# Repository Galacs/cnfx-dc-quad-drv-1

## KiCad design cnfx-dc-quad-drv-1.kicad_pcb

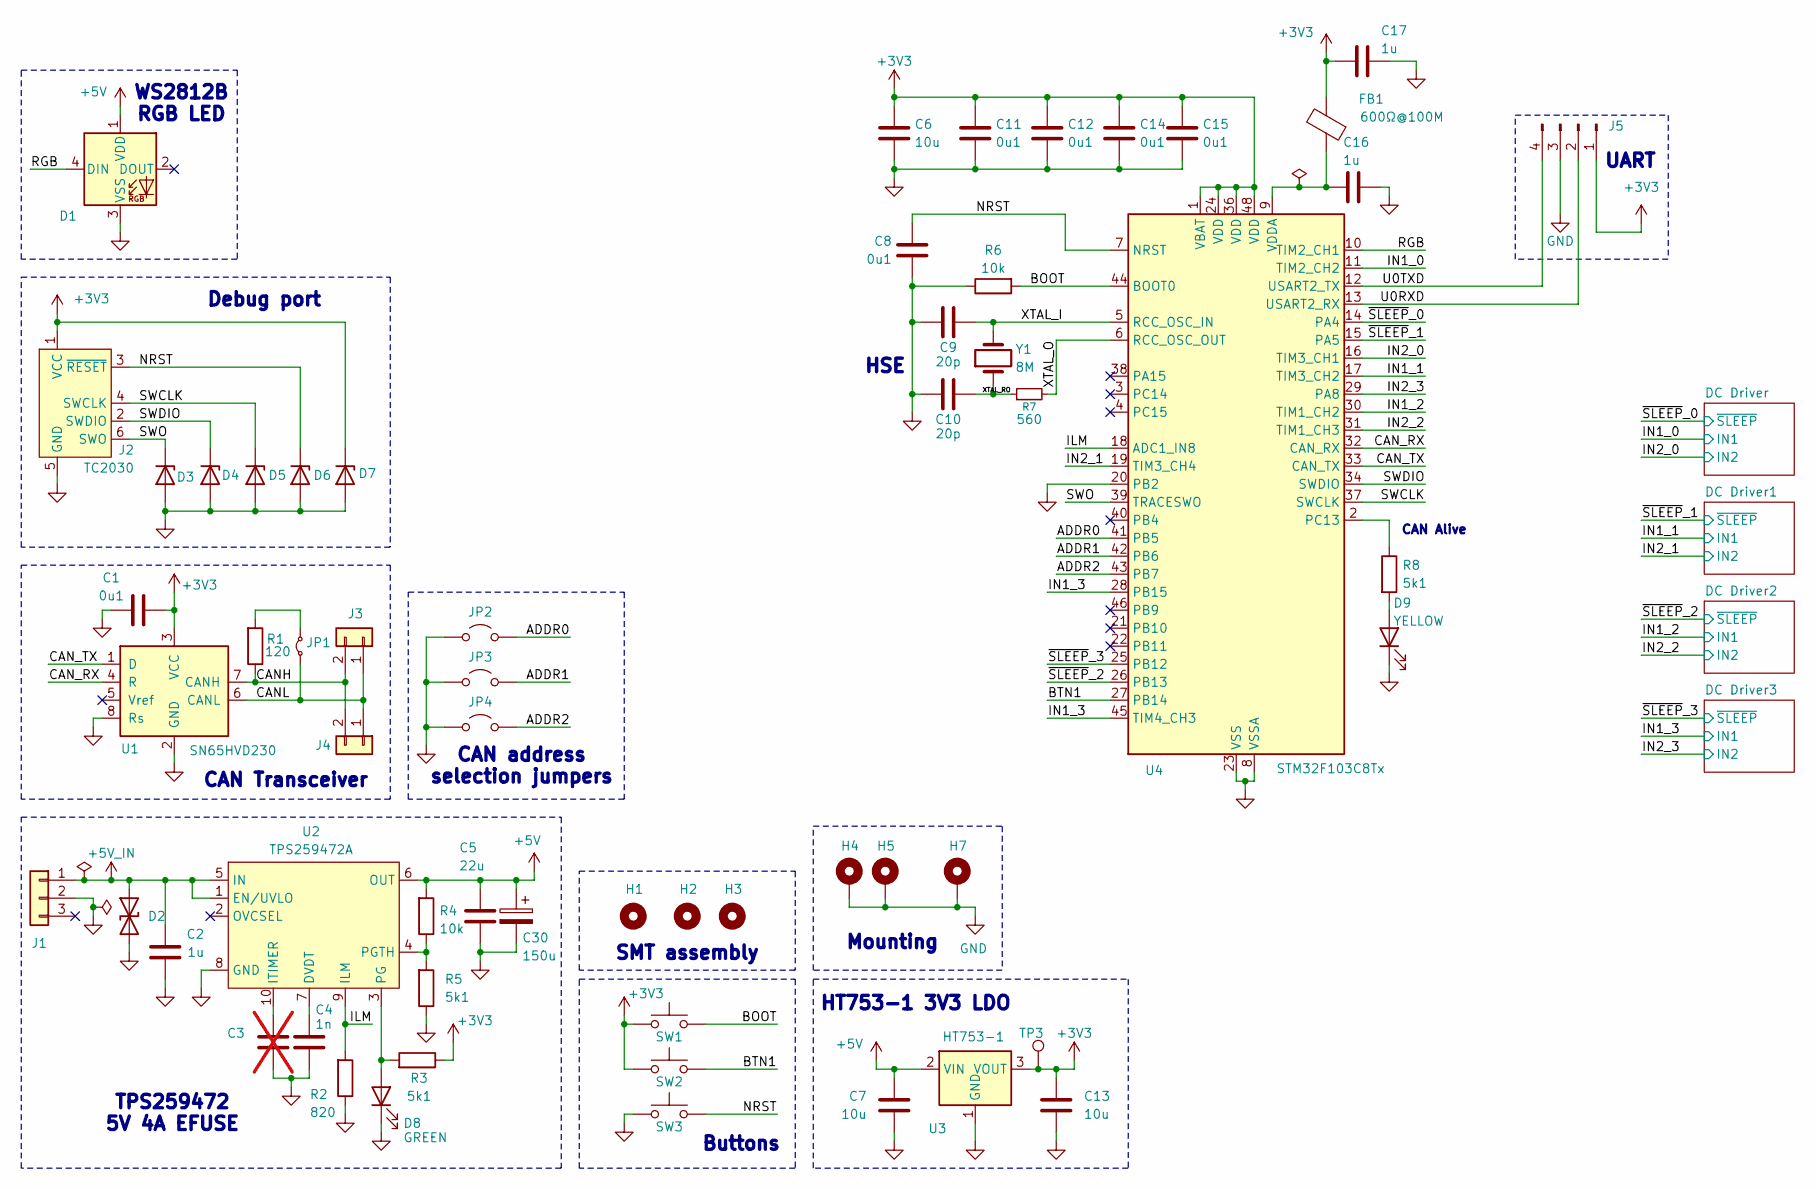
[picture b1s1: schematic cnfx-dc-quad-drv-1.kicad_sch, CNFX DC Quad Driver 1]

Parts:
C1, C8, C11, C12, C14, C15: 0u1; C_0402_1005Metric; Manufacturer Part Number CL05B104KB54PNC; JLCPCB Part # C307331
C2, C16, C17: 1u; C_0402_1005Metric; Manufacturer Part Number CL05A105KA5NQNC; JLCPCB Part # C52923
C3: C; C_0402_1005Metric; not fitted
C4: 1n; C_0402_1005Metric; Manufacturer Part Number 0402B102K500NT; JLCPCB Part # C1523
C5: 22u; C_0805_2012Metric; Manufacturer Part Number CL21A226MAQNNNE; JLCPCB Part # C45783
C6, C7, C13: 10u; C_0805_2012Metric; Manufacturer Part Number GRM21BR61H106KE43L; JLCPCB Part # C440198
C9, C10: 20p; C_0603_1608Metric; Manufacturer Part Number CL10C200JB8NNNC; JLCPCB Part # C1648
C30: 150u; CP_Elec_6.3x7.7; Manufacturer Part Number EEEFTV151XAP; JLCPCB Part # C178603
D1: WS2812B; LED_WS2812B_PLCC4_5.0x5.0mm_P3.2mm; Manufacturer Part Number WS2812B-V5/W; JLCPCB Part # C2874885
D2: SMAJ6.0CA; D_SMA; Manufacturer Part Number SMAJ6.0CA; JLCPCB Part # C19077526
D3, D4, D5, D6, D7: H5VU10U; Diode_DFN1006; Manufacturer Part Number H5VU10U; JLCPCB Part # C22395519
D8: GREEN; LED_0805_2012Metric; Manufacturer Part Number KT-0805G; JLCPCB Part # C2297
D9: YELLOW; LED_0805_2012Metric; Manufacturer Part Number KT-0805Y; JLCPCB Part # C2296
FB1: 600Ω@100M; L_0805_2012Metric; Manufacturer Part Number MPZ2012S601ATD25; JLCPCB Part # C81034
H1, H2, H3: MountingHole; ToolingHole_1.152mm
H4, H5, H7: MountingHole_Pad; MountingHole_3.2mm_M3_Pad_Via
J1: Conn_01x03; JST_XH_B3B-XH-A_1x03_P2.50mm_Vertical; Manufacturer Part Number B3B-XH-A(LF)(SN); JLCPCB Part # C144394
J2: TC2030; Tag-Connect_TC2030-IDC-NL_2x03_P1.27mm_Vertical
J3, J4: Conn_01x02; JST_XH_B2B-XH-A_1x02_P2.50mm_Vertical; Manufacturer Part Number B2B-XH-A(LF)(SN); JLCPCB Part # C158012
J5: Conn_01x04_Pin; PinHeader_1x04_P2.54mm_Vertical
JP1: Jumper_2_Small_Bridged; PinHeader_1x02_P2.54mm_Vertical
JP2, JP3, JP4: Jumper_2_Open; SolderJumper-2_P1.3mm_Open_RoundedPad1.0x1.5mm
R1: 120; R_1206_3216Metric; Manufacturer Part Number 1206W4F1200T5E; JLCPCB Part # C17909
R2: 820; R_0402_1005Metric; Manufacturer Part Number 0402WGF8200TCE; JLCPCB Part # C25135
R3, R5, R8: 5k1; R_0402_1005Metric; Manufacturer Part Number 0402WGF5101TCE; JLCPCB Part # C25905
R4, R6: 10k; R_0402_1005Metric; Manufacturer Part Number 0402WGF1002TCE; JLCPCB Part # C25744
R7: 560; R_0603_1608Metric; Manufacturer Part Number 0603WAF5600T5E; JLCPCB Part # C23204
SW1, SW2, SW3: SW_Push; SW_SPST_TS-1088-xR020; Manufacturer Part Number TS-1088-AR02016; JLCPCB Part # C720477
TP3: TestPoint; TestPoint_Pad_D2.0mm
U1: SN65HVD230; SOIC-8_3.9x4.9mm_P1.27mm; Manufacturer Part Number SN65HVD230DR; JLCPCB Part # C12084
U2: TPS259472A; Texas_RPW0010A_VQFN-HR-10_2x2mm_P0.5mm; Manufacturer Part Number TPS259472ARPWR; JLCPCB Part # C3662789
U3: HT753-1; SOT-89-3; Manufacturer Part Number HT7533-1; JLCPCB Part # C14289
U4: STM32F103C8Tx; LQFP-48_7x7mm_P0.5mm; Manufacturer Part Number STM32F103C8T6; JLCPCB Part # C8734
Y1: 8M; Crystal_SMD_5032-2Pin_5.0x3.2mm; Manufacturer Part Number X50328MSB2GI; JLCPCB Part # C115962

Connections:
+3V3: C1.1, C6.1, C11.1, C12.1, C13.1, C14.1, C15.1, C17.1, D7.1 (K), FB1.2, J2.1 (VCC), J5.1, R3.1, SW1.1, SW2.1, TP3.1 (1_1), U1.3 (VCC), U3.3 (VOUT), U4.1 (VBAT), U4.24 (VDD), U4.36 (VDD), U4.48 (VDD); also elsewhere on the board
+5V: C5.1, C7.1, C30.1, D1.1 (VDD), R4.2, U2.6 (OUT), U3.2 (VIN); also elsewhere on the board
+5V_IN: C2.2, D2.1 (A1), J1.1, U2.1 (EN/UVLO), U2.5 (IN)
/ADDR0: JP2.2 (B), U4.41 (PB5)
/ADDR1: JP3.2 (B), U4.42 (PB6)
/ADDR2: JP4.2 (B), U4.43 (PB7)
/BOOT: R6.2, SW1.2, U4.44 (BOOT0)
/BTN1: SW2.2, U4.27 (PB14)
/CANH: J3.2, J4.2, R1.1, U1.7 (CANH)
/CANL: J3.1, J4.1, JP1.1 (A), U1.6 (CANL)
/CAN_RX: U1.4 (R), U4.32 (CAN_RX)
/CAN_TX: U1.1 (D), U4.33 (CAN_TX)
/ILM: R2.2, U2.9 (ILM), U4.18 (ADC1_IN8)
/IN1_0: U4.11 (TIM2_CH2); also elsewhere on the board
/IN1_1: U4.17 (TIM3_CH2); also elsewhere on the board
/IN1_2: U4.30 (TIM1_CH2); also elsewhere on the board
/IN1_3: U4.28 (PB15), U4.45 (TIM4_CH3); also elsewhere on the board
/IN2_0: U4.16 (TIM3_CH1); also elsewhere on the board
/IN2_1: U4.19 (TIM3_CH4); also elsewhere on the board
/IN2_2: U4.31 (TIM1_CH3); also elsewhere on the board
/IN2_3: U4.29 (PA8); also elsewhere on the board
/NRST: C8.1, D6.1 (K), J2.3 (~RESET), SW3.2, U4.7 (NRST)
/RGB: D1.4 (DIN), U4.10 (TIM2_CH1)
/SWCLK: D5.1 (K), J2.4 (SWCLK), U4.37 (SWCLK)
/SWDIO: D4.1 (K), J2.2 (SWDIO), U4.34 (SWDIO)
/SWO: D3.1 (K), J2.6 (SWO), U4.39 (TRACESWO)
/U0RXD: J5.2, U4.13 (USART2_RX)
/U0TXD: J5.4, U4.12 (USART2_TX)
/XTAL_I: C9.1, U4.5 (RCC_OSC_IN), Y1.2
/XTAL_O: R7.2, U4.6 (RCC_OSC_OUT)
/XTAL_RO: C10.1, R7.1, Y1.1
/~SLEEP_0: U4.14 (PA4); also elsewhere on the board
/~SLEEP_1: U4.15 (PA5); also elsewhere on the board
/~SLEEP_2: U4.26 (PB13); also elsewhere on the board
/~SLEEP_3: U4.25 (PB12); also elsewhere on the board
GND: C1.2, C2.1, C3.2, C4.2, C5.2, C6.2, C7.2, C8.2, C9.2, C10.2, C11.2, C12.2, C13.2, C14.2, C15.2, C16.2, C17.2, C30.2, D1.3 (VSS), D2.2 (A2), D3.2 (A), D4.2 (A), D5.2 (A), D6.2 (A), D7.2 (A), D8.1 (K), D9.1 (K), H4.1 (1_1), H5.1 (1_1), H7.1 (1_1), J1.2, J2.5 (GND), J5.3, JP2.1 (A), JP3.1 (A), JP4.1 (A), R2.1, R5.1, R6.1, SW3.1, U1.2 (GND), U1.8 (Rs), U2.8 (GND), U3.1 (GND), U4.8 (VSSA), U4.20 (PB2), U4.23 (VSS), U4.35 (VSS), U4.47 (VSS); also elsewhere on the board
unnamed: D8.2 (A), R3.2, U2.3 (PG)
unnamed: D9.2 (A), R8.2
unnamed: JP1.2 (B), R1.2
unnamed: C4.1, U2.7 (DVDT)
unnamed: C3.1, U2.10 (ITIMER)
unnamed: R4.1, R5.2, U2.4 (PGTH)
unnamed: R8.1, U4.2 (PC13)
unnamed: C16.1, FB1.1, U4.9 (VDDA)

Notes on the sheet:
SMT assembly
CAN address selection jumpers
Debug port
TPS259472 5V 4A EFUSE
HT753-1 3V3 LDO
CAN Alive
UART
CAN Transceiver
Mounting
WS2812B RGB LED
Buttons
HSE

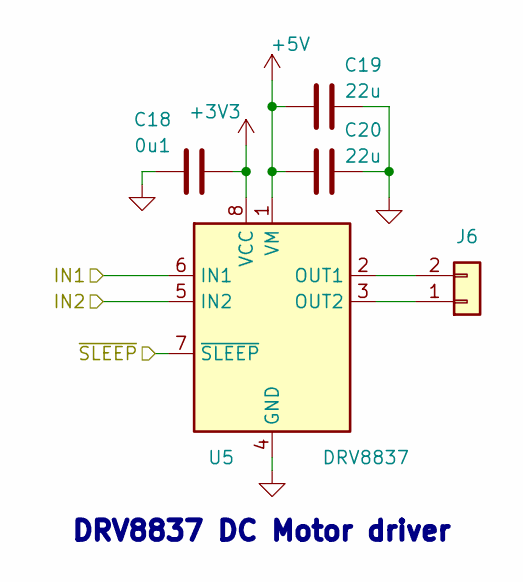
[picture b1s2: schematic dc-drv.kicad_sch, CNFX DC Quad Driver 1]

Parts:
C18: 0u1; C_0402_1005Metric; Manufacturer Part Number CL05B104KB54PNC; JLCPCB Part # C307331
C19, C20: 22u; C_0805_2012Metric; Manufacturer Part Number CL21A226MAQNNNE; JLCPCB Part # C45783
J6: Conn_01x02; JST_XH_B2B-XH-A_1x02_P2.50mm_Vertical; Manufacturer Part Number B2B-XH-A(LF)(SN); JLCPCB Part # C158012
U5: DRV8837; Texas_DSG0008A_WSON-8-1EP_2x2mm_P0.5mm_EP0.9x1.6mm_ThermalV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; Manufacturer Part Number DRV8837DSGR; JLCPCB Part # C39159

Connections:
+3V3: C18.2, U5.8 (VCC); also elsewhere on the board
+5V: C19.2, C20.2, U5.1 (VM); also elsewhere on the board
/IN1_0: U5.6 (IN1); also elsewhere on the board
/IN2_0: U5.5 (IN2); also elsewhere on the board
/~SLEEP_0: U5.7 (~SLEEP); also elsewhere on the board
GND: C18.1, C19.1, C20.1, U5.4 (GND), U5.9 (GND); also elsewhere on the board
unnamed: J6.1, U5.3 (OUT2)
unnamed: J6.2, U5.2 (OUT1)

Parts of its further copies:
C21, C24, C27: 0u1; C_0402_1005Metric; Manufacturer Part Number CL05B104KB54PNC; JLCPCB Part # C307331
C22, C23, C25, C26, C28, C29: 22u; C_0805_2012Metric; Manufacturer Part Number CL21A226MAQNNNE; JLCPCB Part # C45783
J7, J8, J9: Conn_01x02; JST_XH_B2B-XH-A_1x02_P2.50mm_Vertical; Manufacturer Part Number B2B-XH-A(LF)(SN); JLCPCB Part # C158012
U6, U7, U8: DRV8837; Texas_DSG0008A_WSON-8-1EP_2x2mm_P0.5mm_EP0.9x1.6mm_ThermalV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; Manufacturer Part Number DRV8837DSGR; JLCPCB Part # C39159

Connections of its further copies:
+3V3: C21.2, C24.2, C27.2, U6.8 (VCC), U7.8 (VCC), U8.8 (VCC); also elsewhere on the board
+5V: C22.2, C23.2, C25.2, C26.2, C28.2, C29.2, U6.1 (VM), U7.1 (VM), U8.1 (VM); also elsewhere on the board
/IN1_1: U6.6 (IN1); also elsewhere on the board
/IN1_2: U7.6 (IN1); also elsewhere on the board
/IN1_3: U8.6 (IN1); also elsewhere on the board
/IN2_1: U6.5 (IN2); also elsewhere on the board
/IN2_2: U7.5 (IN2); also elsewhere on the board
/IN2_3: U8.5 (IN2); also elsewhere on the board
/~SLEEP_1: U6.7 (~SLEEP); also elsewhere on the board
/~SLEEP_2: U7.7 (~SLEEP); also elsewhere on the board
/~SLEEP_3: U8.7 (~SLEEP); also elsewhere on the board
GND: C21.1, C22.1, C23.1, C24.1, C25.1, C26.1, C27.1, C28.1, C29.1, U6.4 (GND), U6.9 (GND), U7.4 (GND), U7.9 (GND), U8.4 (GND), U8.9 (GND); also elsewhere on the board
unnamed: J7.1, U6.3 (OUT2)
unnamed: J7.2, U6.2 (OUT1)
unnamed: J8.1, U7.3 (OUT2)
unnamed: J8.2, U7.2 (OUT1)
unnamed: J9.1, U8.3 (OUT2)
unnamed: J9.2, U8.2 (OUT1)

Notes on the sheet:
DRV8837 DC Motor driver

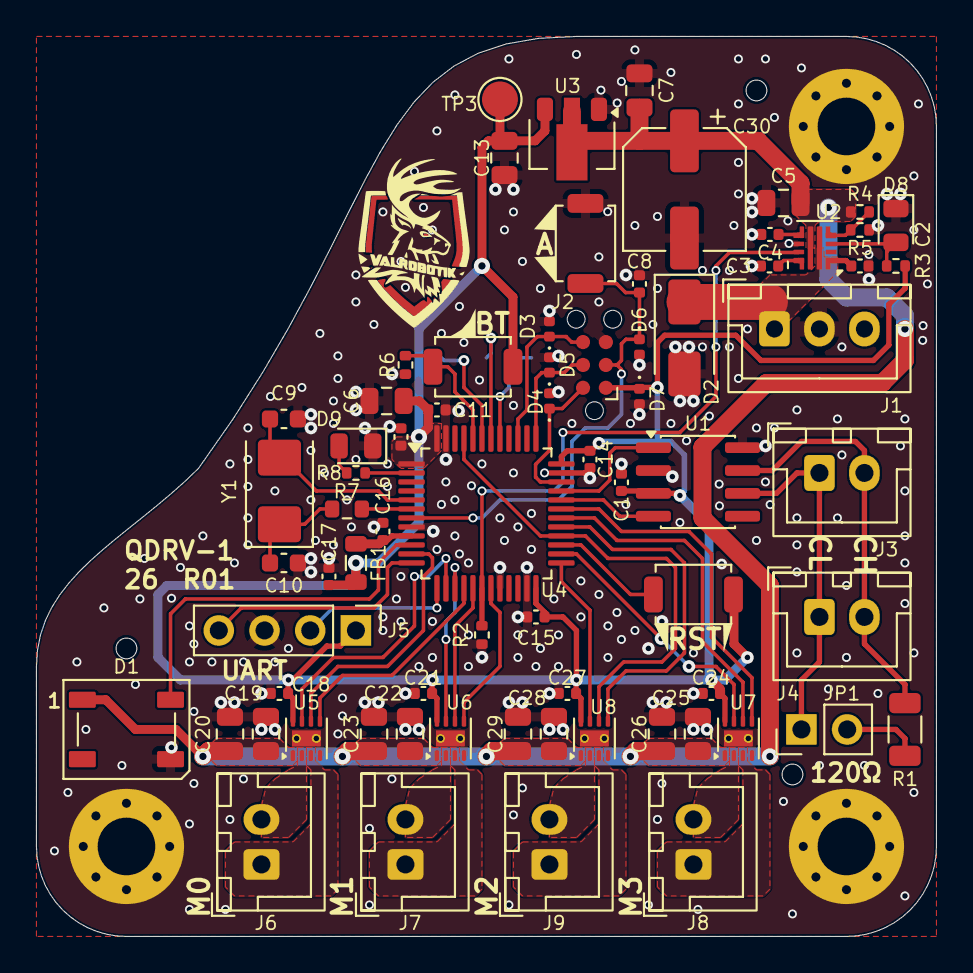
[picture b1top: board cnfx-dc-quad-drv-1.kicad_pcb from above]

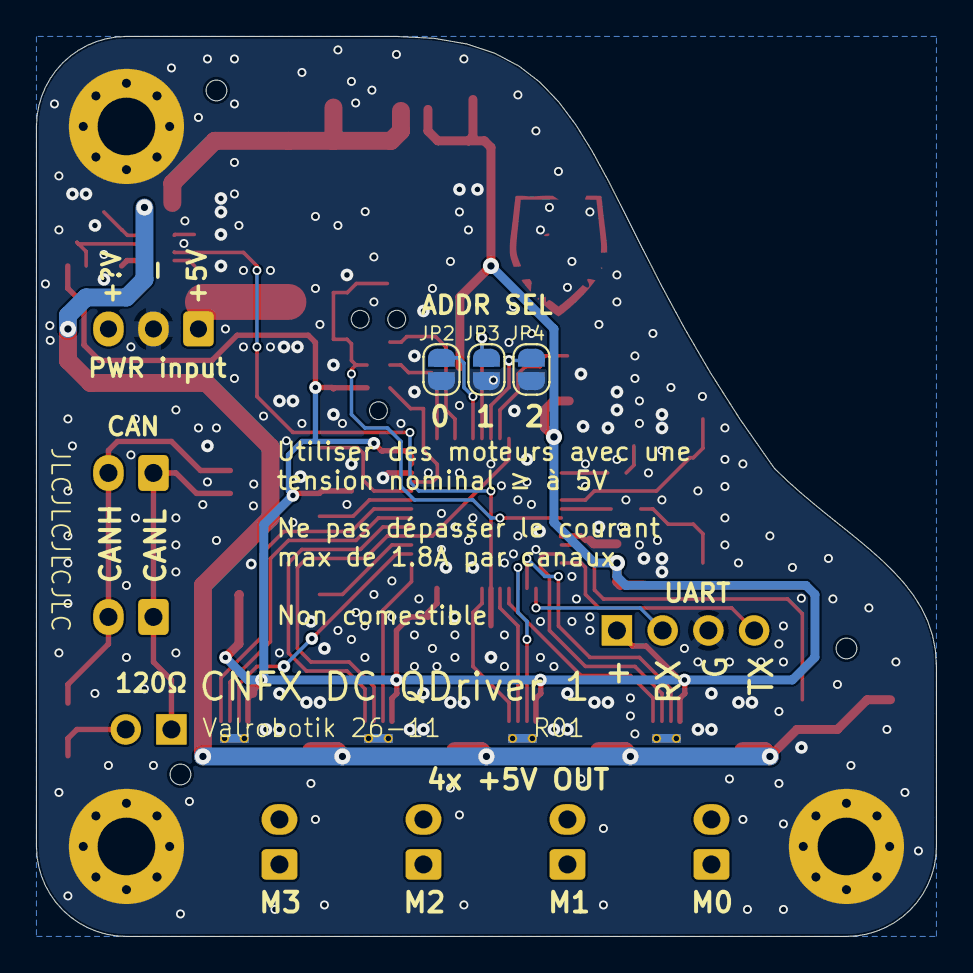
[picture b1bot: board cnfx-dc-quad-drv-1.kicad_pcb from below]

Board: 2 copper layers, 50.0 x 50.0 mm, 80 parts (3 on the bottom side), 52 nets.

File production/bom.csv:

Designator,Footprint,Quantity,Value,LCSC Part #
"C1, C11, C12, C14, C15, C18, C21, C24, C27, C8",0402,10,0u1,C307331
"C10, C9",0603,2,20p,C1648
"C13, C6, C7",0805,3,10u,C440198
"C16, C17, C2",0402,3,1u,C52923
"C19, C20, C22, C23, C25, C26, C28, C29, C5",0805,9,22u,C45783
C30,CP_Elec_6.3x7.7,1,150u,C178603
C4,0402,1,1n,C1523
D1,LED_WS2812B_PLCC4_5.0x5.0mm_P3.2mm,1,WS2812B,C2874885
D2,D_SMA,1,SMAJ6.0CA,C19077526
"D3, D4, D5, D6, D7",Diode_DFN1006,5,H5VU10U,C22395519
D8,0805,1,GREEN,C2297
D9,0805,1,YELLOW,C2296
FB1,0805,1,600Ω@100M,C81034
J1,JST_XH_B3B-XH-A_1x03_P2.50mm_Vertical,1,Conn_01x03,C144394
"J3, J4, J6, J7, J8, J9",JST_XH_B2B-XH-A_1x02_P2.50mm_Vertical,6,Conn_01x02,C158012
R1,1206,1,120,C17909
R2,0402,1,820,C25135
"R3, R5, R8",0402,3,5k1,C25905
"R4, R6",0402,2,10k,C25744
R7,0603,1,560,C23204
"SW1, SW2, SW3",SW_SPST_TS-1088-xR020,3,SW_Push,C720477
U1,SOIC-8_3.9x4.9mm_P1.27mm,1,SN65HVD230,C12084
U2,Texas_RPW0010A_VQFN-HR-10_2x2mm_P0.5mm,1,TPS259472A,C3662789
U3,SOT-89-3,1,HT753-1,C14289
U4,LQFP-48_7x7mm_P0.5mm,1,STM32F103C8Tx,C8734
"U5, U6, U7, U8",Texas_DSG0008A_WSON-8-1EP_2x2mm_P0.5mm_EP0.9x1.6mm_ThermalVias,4,DRV8837,C39159
Y1,Crystal_SMD_5032-2Pin_5.0x3.2mm,1,8M,C115962
